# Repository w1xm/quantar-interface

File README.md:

# quantar-interface
Interfaces a Motorola Quantar repeater to a PC or Raspberry Pi for use with the AllStarLink controller.

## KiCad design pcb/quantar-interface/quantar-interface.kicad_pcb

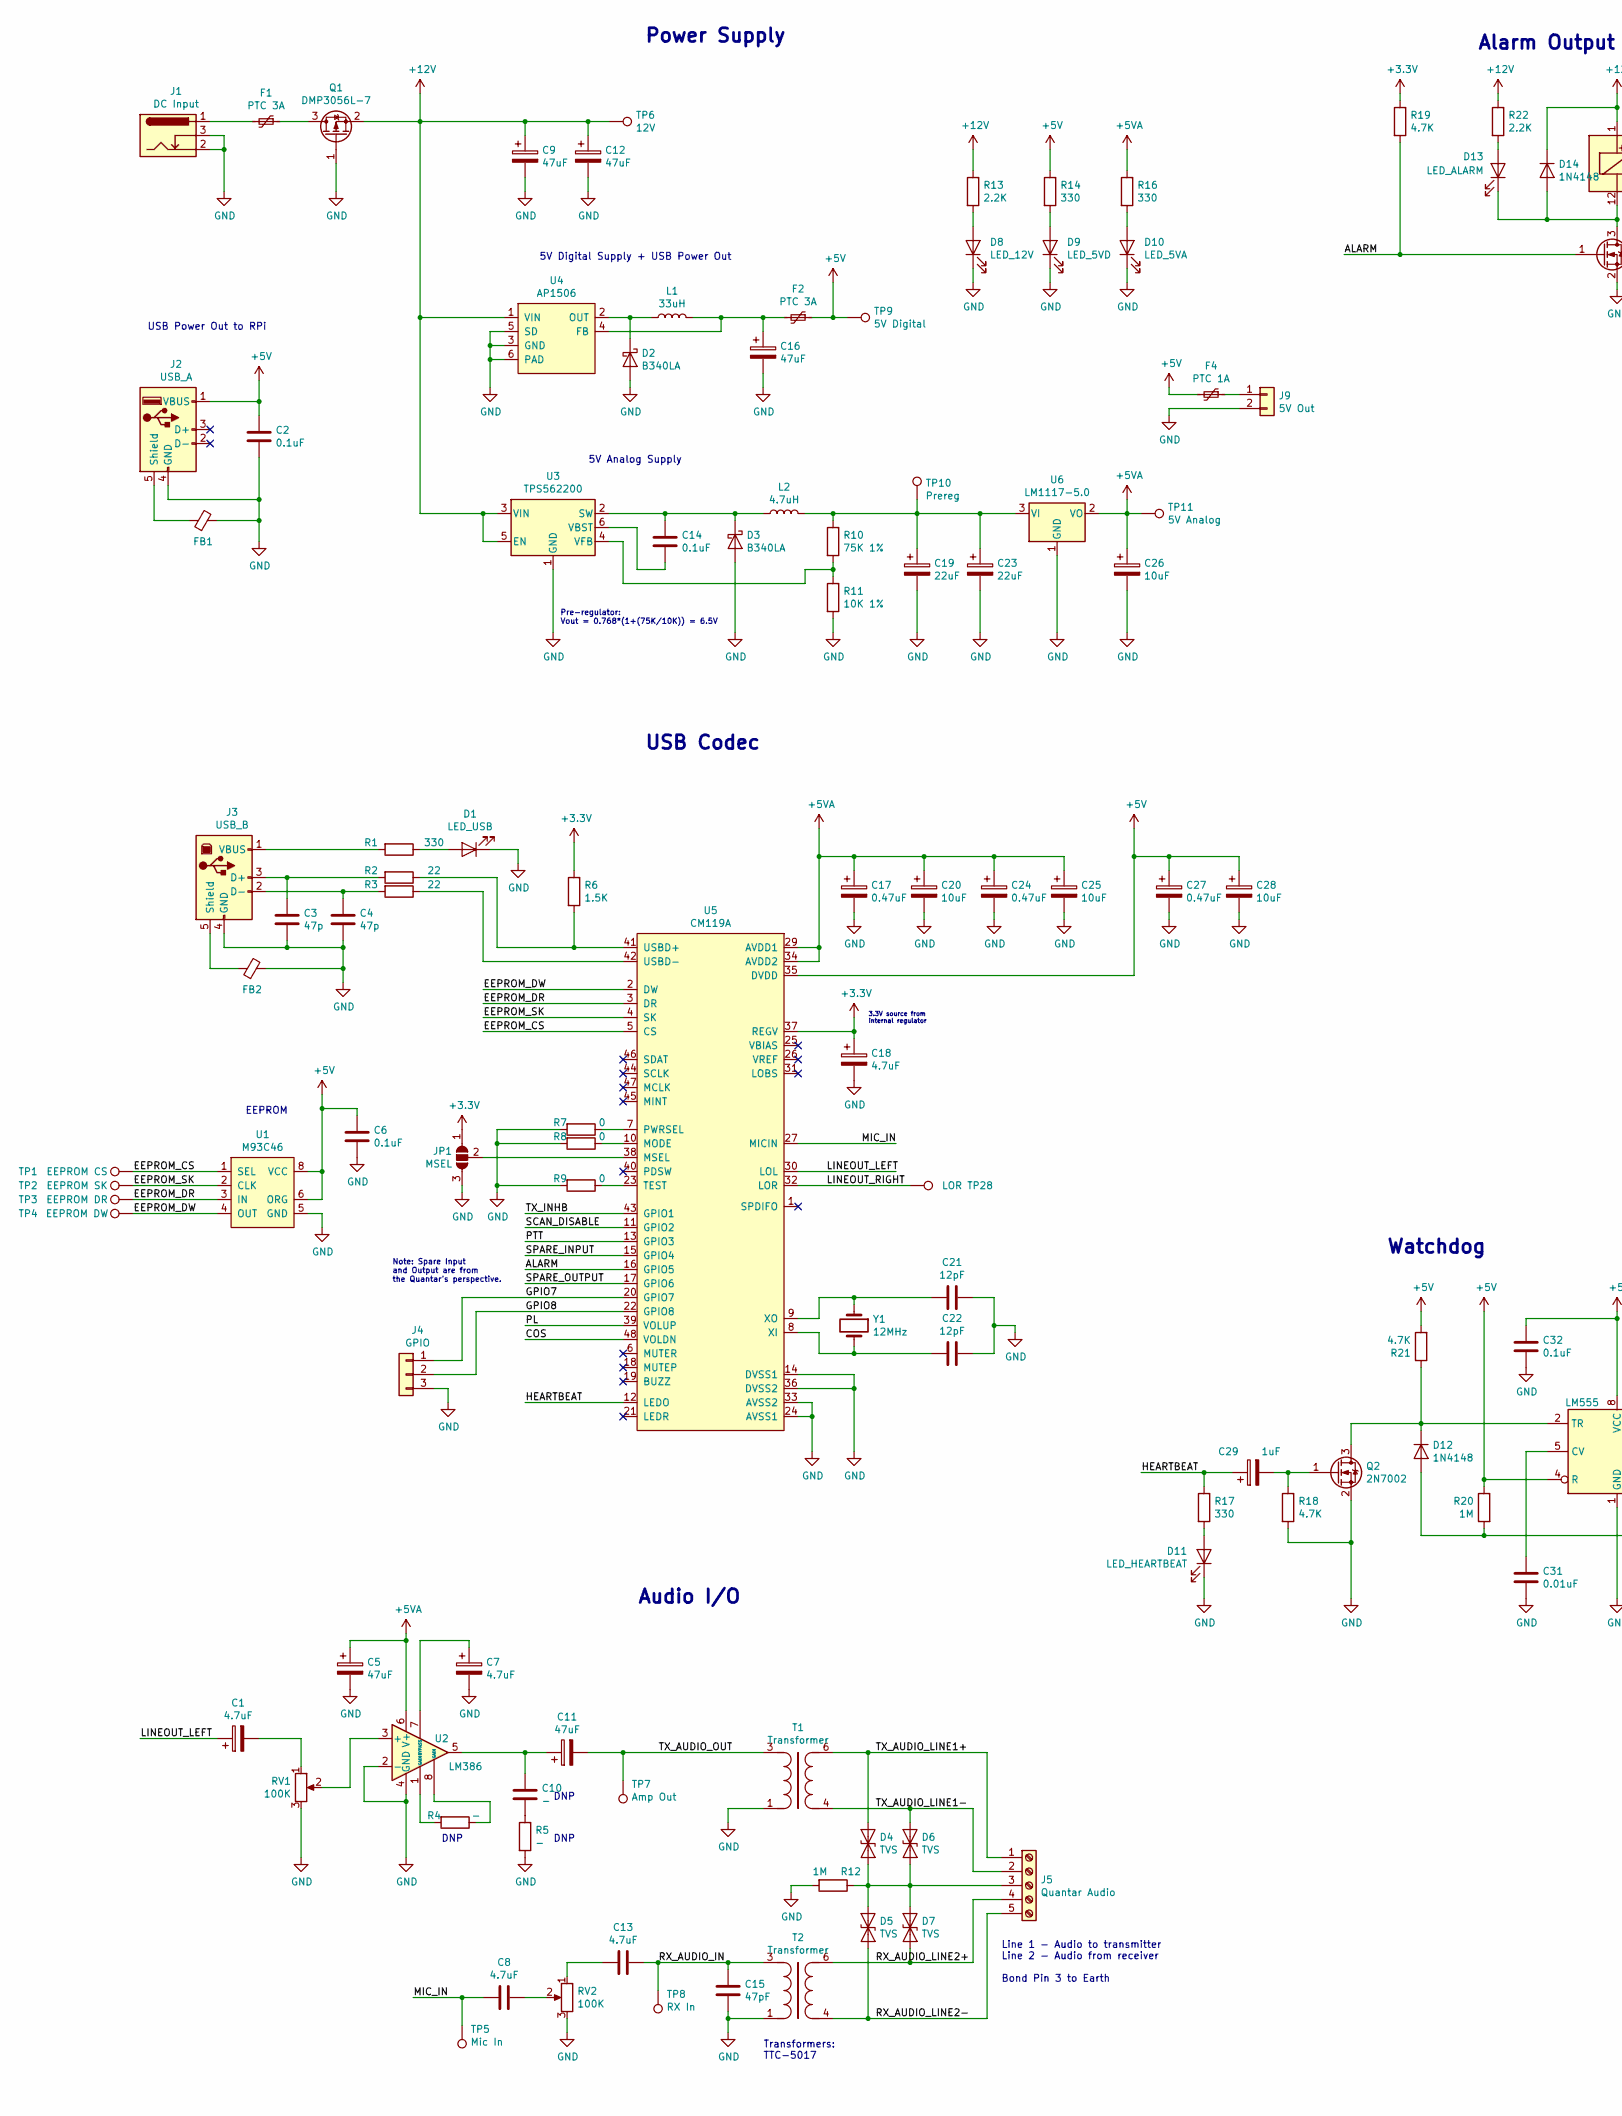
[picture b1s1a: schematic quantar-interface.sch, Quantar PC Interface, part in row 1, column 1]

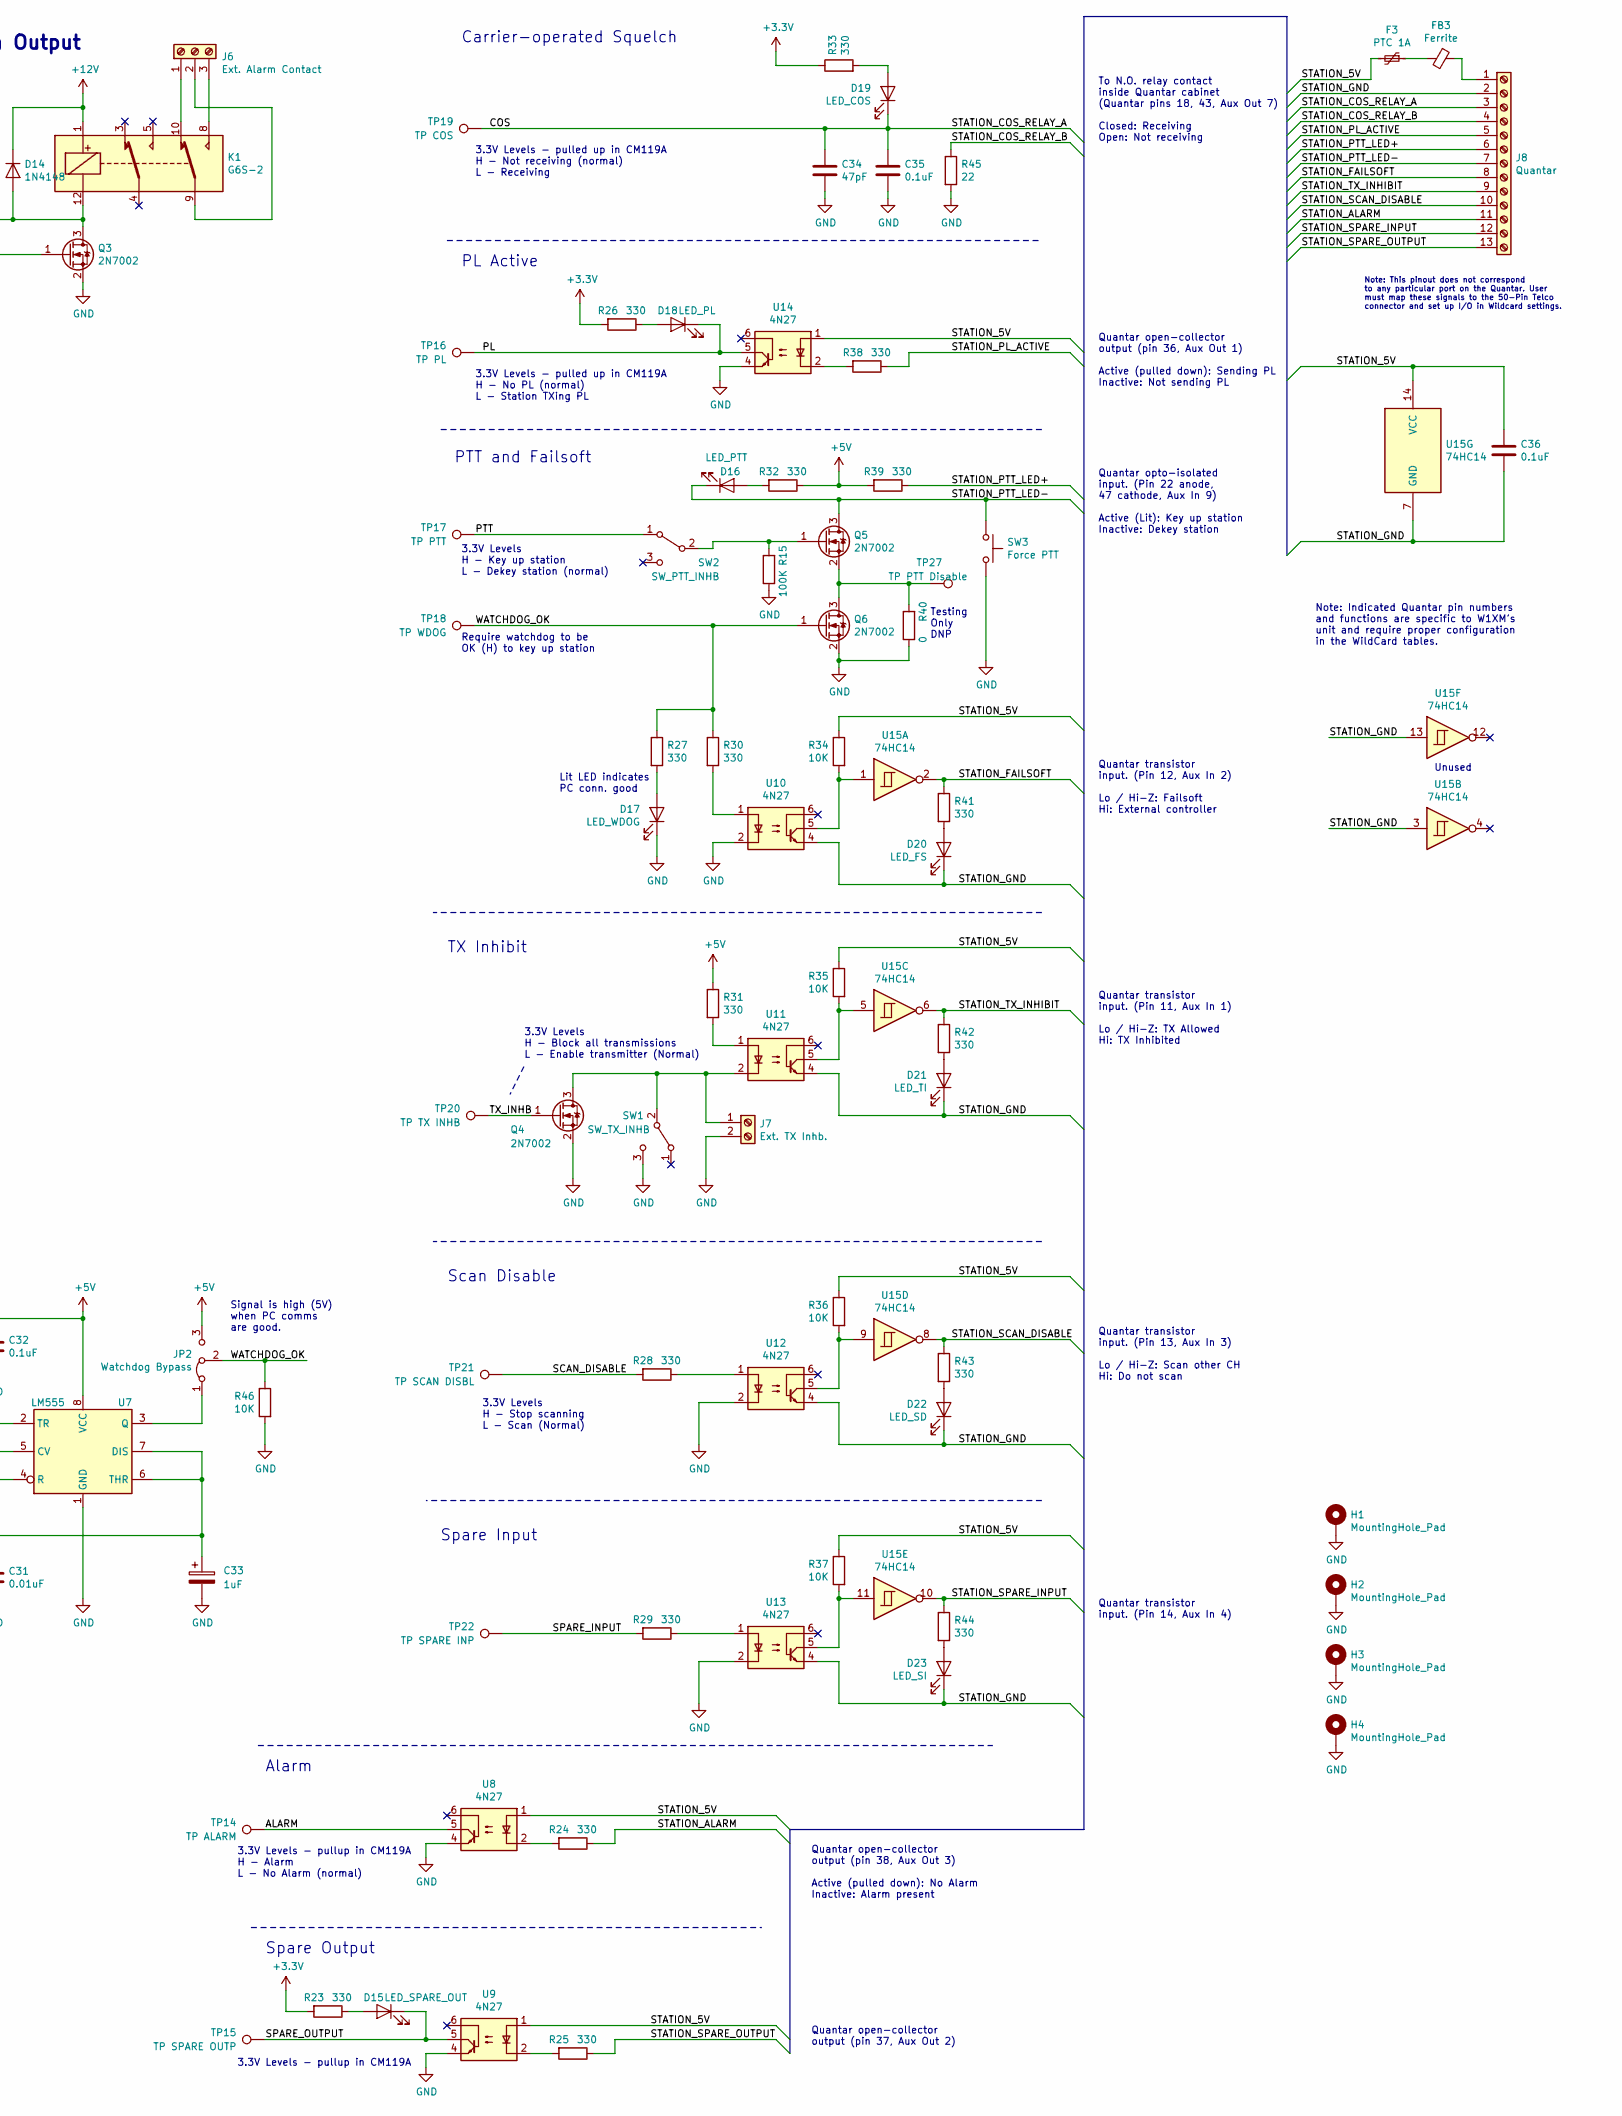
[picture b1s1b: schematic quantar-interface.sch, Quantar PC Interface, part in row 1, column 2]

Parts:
C1, C7, C18: 4.7uF; CP_Elec_4x5.4
C2, C6, C14, C32, C35, C36: 0.1uF; C_0805_2012Metric_Pad1.15x1.40mm_HandSolder
C3, C4: 47p; C_0805_2012Metric_Pad1.15x1.40mm_HandSolder
C5, C9, C11, C12, C16: 47uF; CP_Elec_6.3x5.4
C8, C13: 4.7uF; C_0805_2012Metric_Pad1.15x1.40mm_HandSolder
C10: -; C_0805_2012Metric_Pad1.15x1.40mm_HandSolder
C15, C34: 47pF; C_0805_2012Metric_Pad1.15x1.40mm_HandSolder
C17, C24, C27: 0.47uF; C_1206_3216Metric_Pad1.42x1.75mm_HandSolder
C19, C23: 22uF; CP_Elec_6.3x5.4
C20, C25, C26, C28: 10uF; CP_Elec_4x5.8
C21, C22: 12pF; C_0805_2012Metric_Pad1.15x1.40mm_HandSolder
C29, C33: 1uF; CP_Elec_4x4.5
C31: 0.01uF; C_0805_2012Metric_Pad1.15x1.40mm_HandSolder
D1: LED_USB; LED_0805_2012Metric_Pad1.15x1.40mm_HandSolder
D2, D3: B340LA; D_SMA_Handsoldering
D4, D5, D6, D7: TVS; D_SOD-323_HandSoldering
D8: LED_12V; LED_0805_2012Metric_Pad1.15x1.40mm_HandSolder
D9: LED_5VD; LED_0805_2012Metric_Pad1.15x1.40mm_HandSolder
D10: LED_5VA; LED_0805_2012Metric_Pad1.15x1.40mm_HandSolder
D11: LED_HEARTBEAT; LED_0805_2012Metric_Pad1.15x1.40mm_HandSolder
D12, D14: 1N4148; D_SOD-523
D13: LED_ALARM; LED_0805_2012Metric_Pad1.15x1.40mm_HandSolder
D15: LED_SPARE_OUT; LED_0805_2012Metric_Pad1.15x1.40mm_HandSolder
D16: LED_PTT; LED_0805_2012Metric_Pad1.15x1.40mm_HandSolder
D17: LED_WDOG; LED_0805_2012Metric_Pad1.15x1.40mm_HandSolder
D18: LED_PL; LED_0805_2012Metric_Pad1.15x1.40mm_HandSolder
D19: LED_COS; LED_0805_2012Metric_Pad1.15x1.40mm_HandSolder
D20: LED_FS; LED_0805_2012Metric_Pad1.15x1.40mm_HandSolder
D21: LED_TI; LED_0805_2012Metric_Pad1.15x1.40mm_HandSolder
D22: LED_SD; LED_0805_2012Metric_Pad1.15x1.40mm_HandSolder
D23: LED_SI; LED_0805_2012Metric_Pad1.15x1.40mm_HandSolder
F1, F2: PTC 3A; Fuse_2920_7451Metric_Pad2.10x5.45mm_HandSolder
F3, F4: PTC 1A; Fuse_1210_3225Metric_Pad1.42x2.65mm_HandSolder
FB1, FB2: Ferrite_Bead_Small; L_0805_2012Metric_Pad1.15x1.40mm_HandSolder
FB3: Ferrite; L_0805_2012Metric_Pad1.15x1.40mm_HandSolder
H1, H2, H3, H4: MountingHole_Pad; MountingHole_4mm_Pad_Via
J1: DC Input; BarrelJack_Horizontal
J2: USB_A; USB_A_Stewart_SS-52100-001_Horizontal
J3: USB_B; USB_B_OST_USB-B1HSxx_Horizontal
J4: GPIO; PinHeader_1x03_P2.54mm_Vertical
J5: Quantar Audio; PhoenixContact_MC_1,5_5-G-3.5_1x05_P3.50mm_Horizontal
J6: Ext. Alarm Contact; PhoenixContact_MC_1,5_3-G-3.5_1x03_P3.50mm_Horizontal
J7: Ext. TX Inhb.; PhoenixContact_MC_1,5_2-G-3.5_1x02_P3.50mm_Horizontal
J8: Quantar; PhoenixContact_MC_1,5_13-G-3.5_1x13_P3.50mm_Horizontal
J9: 5V Out; PinHeader_1x02_P2.54mm_Vertical
JP1: MSEL; SolderJumper-3_P1.3mm_Bridged12_RoundedPad1.0x1.5mm_NumberL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
JP2: Watchdog Bypass; PinHeader_1x03_P2.54mm_Vertical
K1: G6S-2; Relay_DPDT_Omron_G6S-2
L1: 33uH; L_12x12mm_H4.5mm
L2: 4.7uH; L_1008_2520Metric
Q1: DMP3056L-7; SOT-23
Q2, Q3, Q4, Q5, Q6: 2N7002; SOT-23
R1, R14, R16, R17, R23, R24, R25, R26, R27, R28, R29, R30, R31, R32, R33, R38, R39, R41, R42, R43, R44: 330; R_0805_2012Metric_Pad1.15x1.40mm_HandSolder
R2, R3, R45: 22; R_0805_2012Metric_Pad1.15x1.40mm_HandSolder
R4, R5: -; R_0805_2012Metric_Pad1.15x1.40mm_HandSolder
R6: 1.5K; R_0805_2012Metric_Pad1.15x1.40mm_HandSolder
R7, R8, R9, R40: 0; R_0805_2012Metric_Pad1.15x1.40mm_HandSolder
R10: 75K 1%; R_0805_2012Metric_Pad1.15x1.40mm_HandSolder
R11: 10K 1%; R_0805_2012Metric_Pad1.15x1.40mm_HandSolder
R12, R20: 1M; R_0805_2012Metric_Pad1.15x1.40mm_HandSolder
R13, R22: 2.2K; R_0805_2012Metric_Pad1.15x1.40mm_HandSolder
R15: 100K; R_0805_2012Metric_Pad1.15x1.40mm_HandSolder
R18, R19, R21: 4.7K; R_0805_2012Metric_Pad1.15x1.40mm_HandSolder
R34, R35, R36, R37, R46: 10K; R_0805_2012Metric_Pad1.15x1.40mm_HandSolder
RV1, RV2: 100K; Potentiometer_Bourns_3296W_Vertical
SW1: SW_TX_INHB; SW_Slide_1P2T_CK_OS102011MS2Q
SW2: SW_PTT_INHB; SW_Slide_1P2T_CK_OS102011MS2Q
SW3: Force PTT; SW_Push_1P1T_NO_CK_KMR2
T1, T2: Transformer
TP1: EEPROM CS; TestPoint_Pad_1.0x1.0mm
TP2: EEPROM SK; TestPoint_Pad_1.0x1.0mm
TP3: EEPROM DR; TestPoint_Pad_1.0x1.0mm
TP4: EEPROM DW; TestPoint_Pad_1.0x1.0mm
TP5: Mic In; TestPoint_Pad_1.0x1.0mm
TP6: 12V; TestPoint_Pad_1.0x1.0mm
TP7: Amp Out; TestPoint_Pad_1.0x1.0mm
TP8: RX In; TestPoint_Pad_1.0x1.0mm
TP9: 5V Digital; TestPoint_Pad_1.0x1.0mm
TP10: Prereg; TestPoint_Pad_1.0x1.0mm
TP11: 5V Analog; TestPoint_Pad_1.0x1.0mm
TP14: TP ALARM; TestPoint_Pad_1.0x1.0mm
TP15: TP SPARE OUTP; TestPoint_Pad_1.0x1.0mm
TP16: TP PL; TestPoint_Pad_1.0x1.0mm
TP17: TP PTT; TestPoint_Pad_1.0x1.0mm
TP18: TP WDOG; TestPoint_Pad_1.0x1.0mm
TP19: TP COS; TestPoint_Pad_1.0x1.0mm
TP20: TP TX INHB; TestPoint_Pad_1.0x1.0mm
TP21: TP SCAN DISBL; TestPoint_Pad_1.0x1.0mm
TP22: TP SPARE INP; TestPoint_Pad_1.0x1.0mm
TP27: TP PTT Disable; TestPoint_Pad_1.0x1.0mm
TP28: LOR; TestPoint_Pad_1.0x1.0mm
U1: M93C46; SO-8_3.9x4.9mm_P1.27mm
U2: LM386; SO-8_3.9x4.9mm_P1.27mm
U3: TPS562200; SOT-23-6
U4: AP1506; TO-263-5_TabPin6
U5: CM119A; LQFP-48_7x7mm_P0.5mm
U6: LM1117-5.0; SOT-223-3_TabPin2
U7: LM555; SOIC-8_3.9x4.9mm_P1.27mm
U8, U9, U10, U11, U12, U13, U14: 4N27; DIP-6_W7.62mm_SMDSocket_SmallPads
U15: 74HC14; SOIC-14_3.9x8.7mm_P1.27mm
Y1: 12MHz; Crystal_SMD_HC49-SD

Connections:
+3V3: C18.1, JP1.1 (A), R6.1, R19.1, R23.2, R26.2, R33.1, U5.37 (REGV)
+5V: C2.1, C6.1, C27.1, C28.1, C32.1, F2.1, F4.2, J2.1 (VBUS), JP2.3 (B), R14.1, R20.1, R21.2, R31.1, R32.1, R39.2, TP9.1, U1.6 (ORG), U1.8 (VCC), U5.35 (DVDD), U7.4 (R), U7.8 (VCC)
+5VA: C5.1, C17.1, C20.1, C24.1, C25.1, C26.1, R16.1, TP11.1, U2.6 (V+), U5.29 (AVDD1), U5.34 (AVDD2), U6.2 (VO)
+12V: C9.1, C12.1, D14.1 (K), K1.1, Q1.2 (S), R13.1, R22.1, TP6.1, U3.3 (VIN), U3.5 (EN), U4.1 (VIN)
/ALARM: Q3.1 (G), R19.2, TP14.1, U5.16 (GPIO5), U8.5
/COS: C34.1, C35.1, D19.1 (K), J8.3, TP19.1, U5.48 (VOLDN)
/EEPROM_CS: TP1.1, U1.1 (SEL), U5.5 (CS)
/EEPROM_DR: TP3.1, U1.3 (IN), U5.3 (DR)
/EEPROM_DW: TP4.1, U1.4 (OUT), U5.2 (DW)
/EEPROM_SK: TP2.1, U1.2 (CLK), U5.4 (SK)
/GPIO7: J4.1, U5.20 (GPIO7)
/GPIO8: J4.2, U5.22 (GPIO8)
/HEARTBEAT: C29.1, R17.1, U5.12 (LEDO)
/LINEOUT_LEFT: C1.1, U5.30 (LOL)
/LINEOUT_RIGHT: TP28.1, U5.32 (LOR)
/MIC_IN: C8.2, TP5.1, U5.27 (MICIN)
/PL: D18.1 (K), TP16.1, U5.39 (VOLUP), U14.5
/PTT: SW2.1 (A), TP17.1, U5.13 (GPIO3)
/RX_AUDIO_IN: C13.1, C15.1, T2.3, TP8.1
/RX_AUDIO_LINE2+: D7.2 (A2), J5.4, T2.6
/RX_AUDIO_LINE2-: D5.2 (A2), J5.5, T2.4
/SCAN_DISABLE: R28.2, TP21.1, U5.11 (GPIO2)
/SPARE_INPUT: R29.2, TP22.1, U5.15 (GPIO4)
/SPARE_OUTPUT: D15.1 (K), TP15.1, U5.17 (GPIO6), U9.5
/STATION_5V: C36.1, F3.2, R34.1, R35.1, R36.1, R37.1, U8.1, U9.1, U14.1, U15.14 (VCC)
/STATION_ALARM: J8.11, R24.1
/STATION_COS_RELAY_B: J8.4, R45.1
/STATION_FAILSOFT: J8.8, R41.1, U15.2
/STATION_GND: C36.2, D20.1 (K), D21.1 (K), D22.1 (K), D23.1 (K), J8.2, U10.4, U11.4, U12.4, U13.4, U15.3, U15.7 (GND), U15.13
/STATION_PL_ACTIVE: J8.5, R38.1
/STATION_PTT_LED+: J8.6, R39.1
/STATION_PTT_LED-: D16.1 (K), J8.7, Q5.3 (D), SW3.1
/STATION_SCAN_DISABLE: J8.10, R43.1, U15.8
/STATION_SPARE_INPUT: J8.12, R44.1, U15.10
/STATION_SPARE_OUTPUT: J8.13, R25.1
/STATION_TX_INHIBIT: J8.9, R42.1, U15.6
/TX_AUDIO_LINE1+: D4.1 (A1), J5.1, T1.6
/TX_AUDIO_LINE1-: D6.1 (A1), J5.2, T1.4
/TX_AUDIO_OUT: C11.2, T1.3, TP7.1
/TX_INHB: Q4.1 (G), TP20.1, U5.43 (GPIO1)
/WATCHDOG_OK: JP2.2 (C), Q6.1 (G), R27.1, R30.1, R46.1, TP18.1
GND: C2.2, C3.2, C4.2, C5.2, C6.2, C7.2, C9.2, C12.2, C15.2, C16.2, C17.2, C18.2, C19.2, C20.2, C21.2, C22.2, C23.2, C24.2, C25.2, C26.2, C27.2, C28.2, C31.2, C32.2, C33.2, C34.2, C35.2, D1.1 (K), D2.2 (A), D3.2 (A), D8.1 (K), D9.1 (K), D10.1 (K), D11.1 (K), D17.1 (K), FB1.2, FB2.2, H1.1, H2.1, H3.1, H4.1, J1.2, J1.3, J2.4 (GND), J3.4 (GND), J4.3, J7.2, J9.2, JP1.3 (B), Q1.1 (G), Q2.2 (S), Q3.2 (S), Q4.2 (S), Q6.2 (S), R5.2, R7.2, R8.2, R9.2, R11.2, R12.2, R15.1, R18.2, R40.1, R45.2, R46.2, RV1.3, RV2.3, SW1.3 (C), SW3.2, T1.1, T2.1, U1.5 (GND), U2.2 (-), U2.4 (GND), U3.1 (GND), U4.3 (GND), U4.5 (SD), U4.6 (PAD), U5.14 (DVSS1), U5.24 (AVSS1), U5.33 (AVSS2), U5.36 (DVSS2), U6.1 (GND), U7.1 (GND), U8.4, U9.4, U10.2, U12.2, U13.2, U14.4
unnamed: C1.2, RV1.1
unnamed: C3.1, J3.3 (D+), R2.2
unnamed: C4.1, J3.2 (D-), R3.2
unnamed: C7.1, U2.7 (BYPASS)
unnamed: C8.1, RV2.2
unnamed: C10.1, C11.1, U2.5
unnamed: C10.2, R5.1
unnamed: C13.2, RV2.1
unnamed: C14.1, D3.1 (K), L2.1, U3.2 (SW)
unnamed: C14.2, U3.6 (VBST)
unnamed: C16.1, F2.2, L1.2, U4.4 (FB)
unnamed: C19.1, C23.1, L2.2, R10.1, TP10.1, U6.3 (VI)
unnamed: C21.1, U5.9 (XO), Y1.1
unnamed: C22.1, U5.8 (XI), Y1.2
unnamed: C29.2, Q2.1 (G), R18.1
unnamed: C31.1, U7.5 (CV)
unnamed: C33.1, D12.2 (A), R20.2, U7.6 (THR), U7.7 (DIS)
unnamed: D1.2 (A), R1.1
unnamed: D2.1 (K), L1.1, U4.2 (OUT)
unnamed: D4.2 (A2), D5.1 (A1), D6.2 (A2), D7.1 (A1), J5.3, R12.1
unnamed: D8.2 (A), R13.2
unnamed: D9.2 (A), R14.2
unnamed: D10.2 (A), R16.2
unnamed: D11.2 (A), R17.2
unnamed: D12.1 (K), Q2.3 (D), R21.1, U7.2 (TR)
unnamed: D13.1 (K), D14.2 (A), K1.12, Q3.3 (D)
unnamed: D13.2 (A), R22.2
unnamed: D15.2 (A), R23.1
unnamed: D16.2 (A), R32.2
unnamed: D17.2 (A), R27.2
unnamed: D18.2 (A), R26.1
unnamed: D19.2 (A), R33.2
unnamed: D20.2 (A), R41.2
unnamed: D21.2 (A), R42.2
unnamed: D22.2 (A), R43.2
unnamed: D23.2 (A), R44.2
unnamed: F1.1, Q1.3 (D)
unnamed: F1.2, J1.1
unnamed: F3.1, FB3.2
unnamed: F4.1, J9.1
unnamed: FB1.1, J2.5 (Shield)
unnamed: FB2.1, J3.5 (Shield)
unnamed: FB3.1, J8.1
unnamed: J3.1 (VBUS), R1.2
unnamed: J6.1, K1.10
unnamed: J6.2, K1.9
unnamed: J6.3, K1.8
unnamed: J7.1, Q4.3 (D), SW1.2 (B), U11.2
unnamed: JP1.2 (C), U5.38 (MSEL)
unnamed: JP2.1 (A), U7.3 (Q)
unnamed: Q5.1 (G), R15.2, SW2.2 (B)
unnamed: Q5.2 (S), Q6.3 (D), R40.2, TP27.1
unnamed: R2.1, R6.2, U5.41 (USBD+)
unnamed: R3.1, U5.42 (USBD-)
unnamed: R4.1, U2.8 (GAIN)
unnamed: R4.2, U2.1 (GAIN)
unnamed: R7.1, U5.7 (PWRSEL)
unnamed: R8.1, U5.10 (MODE)
unnamed: R9.1, U5.23 (TEST)
unnamed: R10.2, R11.1, U3.4 (VFB)
unnamed: R24.2, U8.2
unnamed: R25.2, U9.2
unnamed: R28.1, U12.1
unnamed: R29.1, U13.1
unnamed: R30.2, U10.1
unnamed: R31.2, U11.1
unnamed: R34.2, U10.5, U15.1
unnamed: R35.2, U11.5, U15.5
unnamed: R36.2, U12.5, U15.9
unnamed: R37.2, U13.5, U15.11
unnamed: R38.2, U14.2
unnamed: RV1.2, U2.3 (+)

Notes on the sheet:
Line 1 - Audio to transmitter Line 2 - Audio from receiver Bond Pin 3 to Earth
5V Digital Supply + USB Power Out
5V Analog Supply
Pre-regulator: Vout = 0.768*(1+(75K/10K)) = 6.5V
Power Supply
USB Power Out to RPi
EEPROM
3.3V source from internal regulator
DNP
Transformers: TTC-5017
Audio I/O
Carrier-operated Squelch
3.3V Levels - pulled up in CM119A H - Not receiving (normal) L - Receiving
To N.O. relay contact inside Quantar cabinet (Quantar pins 18, 43, Aux Out 7) Closed: Receiving Open: Not receiving
Quantar opto-isolated input. (Pin 22 anode, 47 cathode, Aux In 9) Active (Lit): Key up station Inactive: Dekey station
3.3V Levels - pulled up in CM119A H - No PL (normal) L - Station TXing PL
PL Active
PTT and Failsoft
3.3V Levels H - Key up station L - Dekey station (normal)
Require watchdog to be OK (H) to key up station
Testing Only DNP
Quantar open-collector output (pin 36, Aux Out 1) Active (pulled down): Sending PL Inactive: Not sending PL
Quantar transistor input. (Pin 12, Aux In 2) Lo / Hi-Z: Failsoft Hi: External controller
Note: Indicated Quantar pin numbers and functions are specific to W1XM’s unit and require proper configuration in the WildCard tables.
Lit LED indicates PC conn. good
TX Inhibit
Quantar transistor input. (Pin 11, Aux In 1) Lo / Hi-Z: TX Allowed Hi: TX Inhibited
Scan Disable
3.3V Levels H - Block all transmissions L - Enable transmitter (Normal)
Quantar transistor input. (Pin 13, Aux In 3) Lo / Hi-Z: Scan other CH Hi: Do not scan
3.3V Levels H - Stop scanning L - Scan (Normal)
Spare Input
Quantar transistor input. (Pin 14, Aux In 4)
3.3V Levels - pullup in CM119A H - Alarm L - No Alarm (normal)
Alarm
Spare Output
Quantar open-collector output (pin 37, Aux Out 2)
USB Codec
Watchdog
Note: This pinout does not correspond to any particular port on the Quantar. User must map these signals to the 50-Pin Telco connector and set up I/O in Wildcard settings.

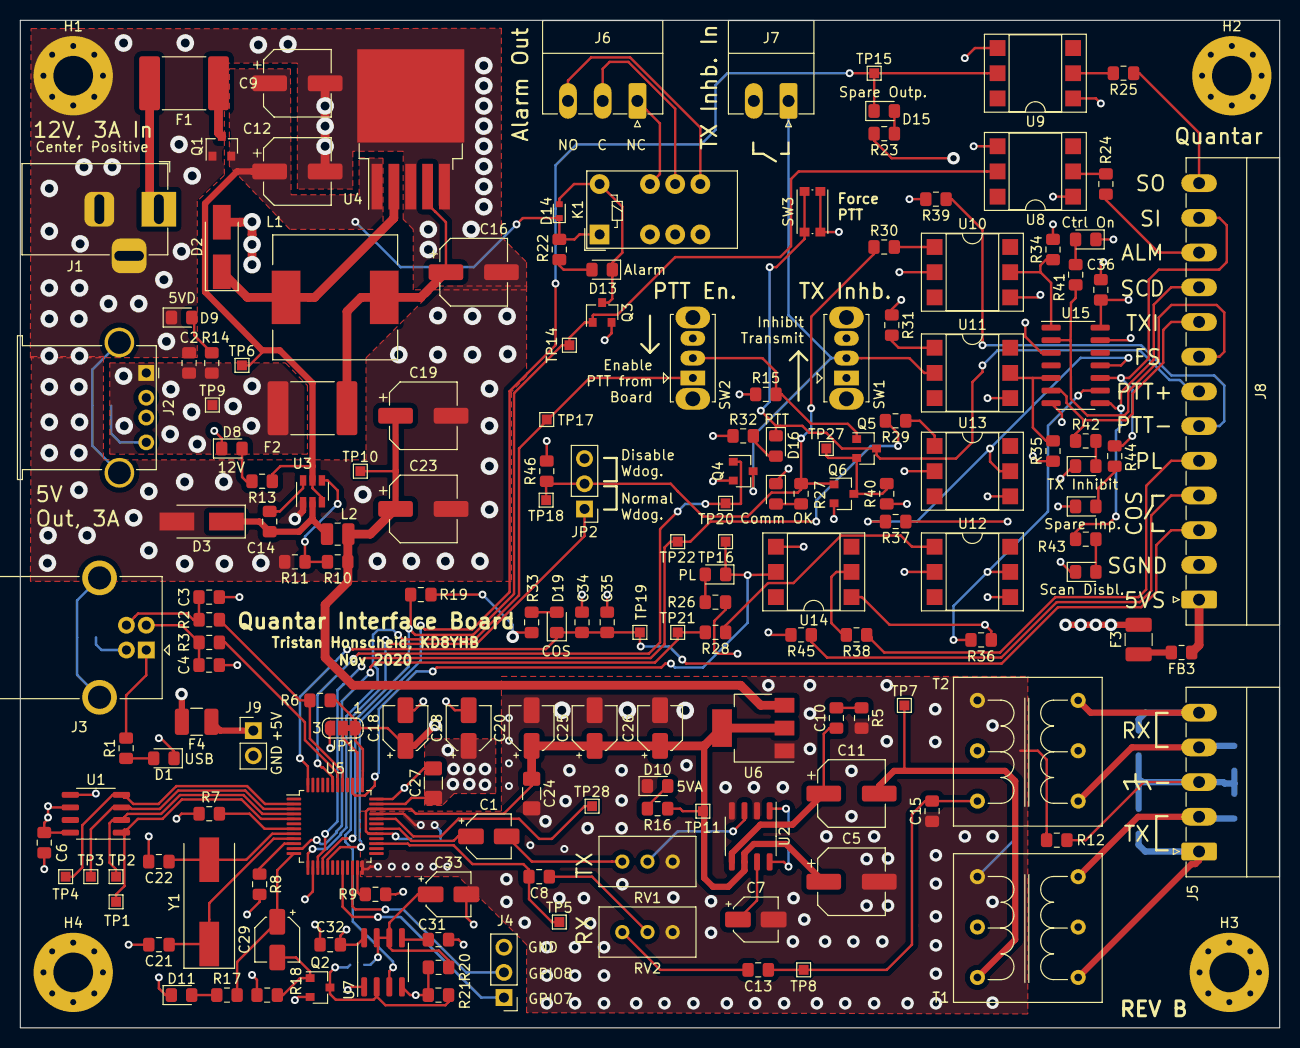
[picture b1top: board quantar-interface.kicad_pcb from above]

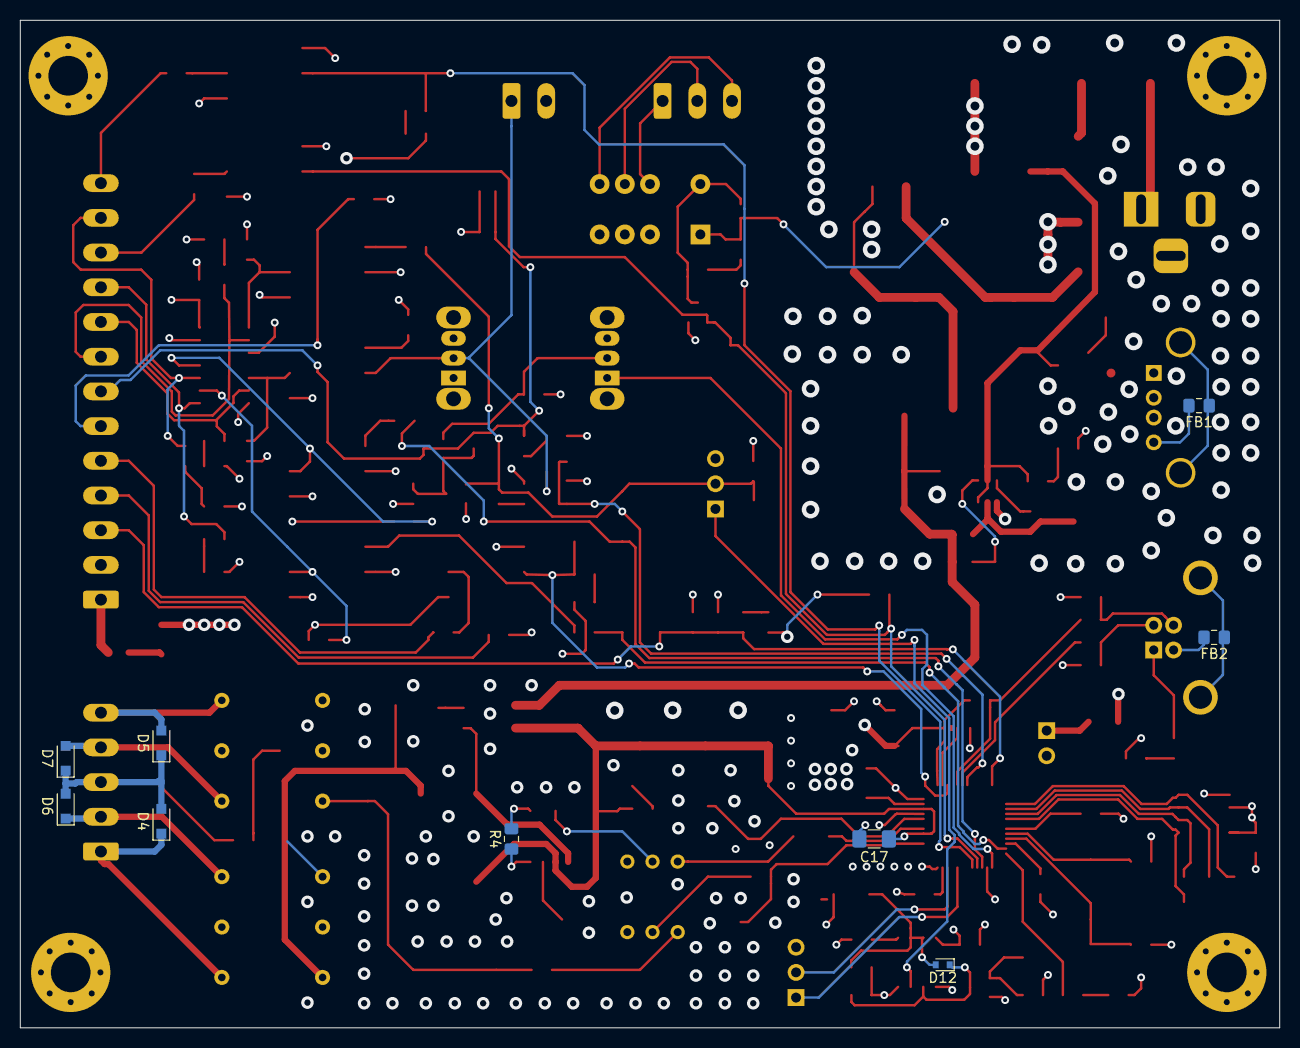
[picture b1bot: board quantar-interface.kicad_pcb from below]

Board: 4 copper layers, 127.0 x 101.6 mm, 180 parts (9 on the bottom side), 114 nets.

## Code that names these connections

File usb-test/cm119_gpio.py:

"""
USB HID interface to CM119 GPIO pins

Tristan Honscheid KD8YHB
6 Dec 2020
"""

import hid

# This should be compatible with the CM108, too --Use PID 0x000C
CM119_USB_VID = 0x0D8C
CM119_USB_PID = 0x013A

#
# HID Input Report (4 bytes)
#
# - Byte 0
#    0000.0000
#    |||| |||+------ VOLUP pressed (0), released (1)
#    |||| ||+------- VOLDN pressed (0), released (1)
#    |||| |+-------- Playback/Mute button* pressed (1), no activity (0)
#    |||| +--------- Record/Mute button* pressed (1), no activity (0)
#    ||++----------- Generic register written by Host MCU (not used)
#    ++------------- 00. Byte 1 caries general purpose input (what we use)
#                    01. Bytes 0-3 are generic HID registers
#                    10. Values written to Bytes 0-3 are also mapped to
#                        MCU_CTRL and EEPROM registers. (see datasheet page 17)
#                    11. Reserved
#    * This input not connected on board.
# - Byte 1 - GPIO input register
#    0000.0000
#    |       +------ GPIO1 input (1=high, 0=low)
#    |               ...
#    +-------------- GPIO8
# - Byte 2 - Generic register writen by host MCU (not used)
# - Byte 3 - Generic register writen by host MCU (not used)
#

#
# HID Output Report (1 byte report number + 4 bytes payload)
#
# - Byte 0 - Report number. Has value of 0x00
# - Byte 1 - Mode, buzzer, and SPDIF
#    0000.0000
#    |||| ++++------ SPDIF status channel (not used)
#    |||+----------- SPDIF valid bit (not used)
#    ||+------------ Buzzer control (1=on, 0=off)
#    ++------------- 00. Report carries GPIO commands. (what we use)
#                    01. Bytes 1-4 are generic HID registers
#                    10. Bytes 1-4 are mapped to MCU_CRTL and EEPROM
#                       registers (see datasheet page 18)
#                    11. Reserved
# - Byte 2 - GPIO output drivers
#    0000.0000
#    |       +------ GPIO1 output (1=high, 0=low)
#    |               ...
#    +-------------- GPIO8
# - Byte 3 - GPIO data direction register
#    0000.0000
#    |       +------ GPIO1 dir (1=output, 0=input) Input is default
#    |               ...
#    +-------------- GPIO8
# - Byte 4 - SPDIF category byte (not used)
#


class CM119_IO(hid.Device):
    """
    Manages a CM119's GPIO via USB HID
    """

    def __init__(self, vid=CM119_USB_VID, pid=CM119_USB_PID):
        """ Open the device. """
        # Maintain a record of our HID output report so we can modify individual pins. Array
        # holds Report Number (0x00), followed by 4 report bytes
        self.output_report = bytearray(5)

        # Init superclass
        super().__init__(vid, pid)

    def set_dir(self, pin_modes: dict):
        """
        Configure the GPIO in the device.
        :param: pin_modes A dictionary of the form {1: "I", 2: "O"}, etc. Pins not included
                do not change state. GPIOs are numbered 1-8.
        """
        # Configure inputs/outputs
        for key, val in pin_modes.items():
            if not (1 <= key <= 8):
                raise ValueError(f"Illegal GPIO number: {key}")
            if val == "O":
                # If output, set bit
                self.output_report[3] |= 1 << (key - 1)
            else:
                # If input, clear bit
                self.output_report[3] &= ~(1 << (key - 1))

        self.write(bytes(self.output_report))

    def set_output(self, gpio_num: int, state: bool):
        """
        Sets a GPIO output
        :param: gpio_num    The GPIO pin number to adjust (range 1-8)
        :param: state       True for on/high, False for off/low
        """
        if not (1 <= gpio_num <= 8):
            raise ValueError(f"Illegal GPIO number: {gpio_num}")
        if state:
            # Set output
            self.output_report[2] |= 1 << (gpio_num - 1)
        else:
            # Clear output
            self.output_report[2] &= ~(1 << (gpio_num - 1))

        self.write(bytes(self.output_report))

    def read_inputs(self):
        """
        Waits for an HID interrupt w/ an Input Report.
        """
        input_report = self.read(4)
        assert (
            input_report[0] & 0xC0 == 0x00
        )  # Make sure this a GPIO input report (bits 7:6 clear)

        # Quantar Interface board doesn't use Mute/Playback or Mute/Record buttons, but those could be
        # easily added. See input report description at top of file.
        pin_states = {
            "VOLDN": bool(input_report[0] & 0x02),
            "VOLUP": bool(input_report[0] & 0x01),
            "GPIO1": bool(input_report[1] & 0x01),
            "GPIO2": bool(input_report[1] & 0x02),
            "GPIO3": bool(input_report[1] & 0x04),
            "GPIO4": bool(input_report[1] & 0x08),
            "GPIO5": bool(input_report[1] & 0x10),
            "GPIO6": bool(input_report[1] & 0x20),
            "GPIO7": bool(input_report[1] & 0x40),
            "GPIO8": bool(input_report[1] & 0x80),
        }

        return pin_states

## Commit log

2020-08-06 Good chunk of schematic including first draft of audio circuitry
2020-11-05 Done with schematic, ready to route
2020-11-05 Correct package for 74HC14; Number the pad for the AP1506
2020-11-08 Schematic revisions, first draft of layout
2020-11-08 Add fiducials for PCBA
2020-11-08 Add crappy notes of DK part numbers for later BOM
2020-11-08 Add bottom layer plane to analog area
2020-11-14 Add BOM
2020-11-15 Plot gerbers, generate JLCPCB BOM and picklist, move all JLC components to top side
2020-12-05 BOM as ordered. Minor changes based on availability
2020-12-05 PCBA files for REV A
2020-12-05 Revision B
2020-12-07 EEPROM bin file and docs
2020-12-07 Add Python code for testing CM119 GPIO via USB HID
